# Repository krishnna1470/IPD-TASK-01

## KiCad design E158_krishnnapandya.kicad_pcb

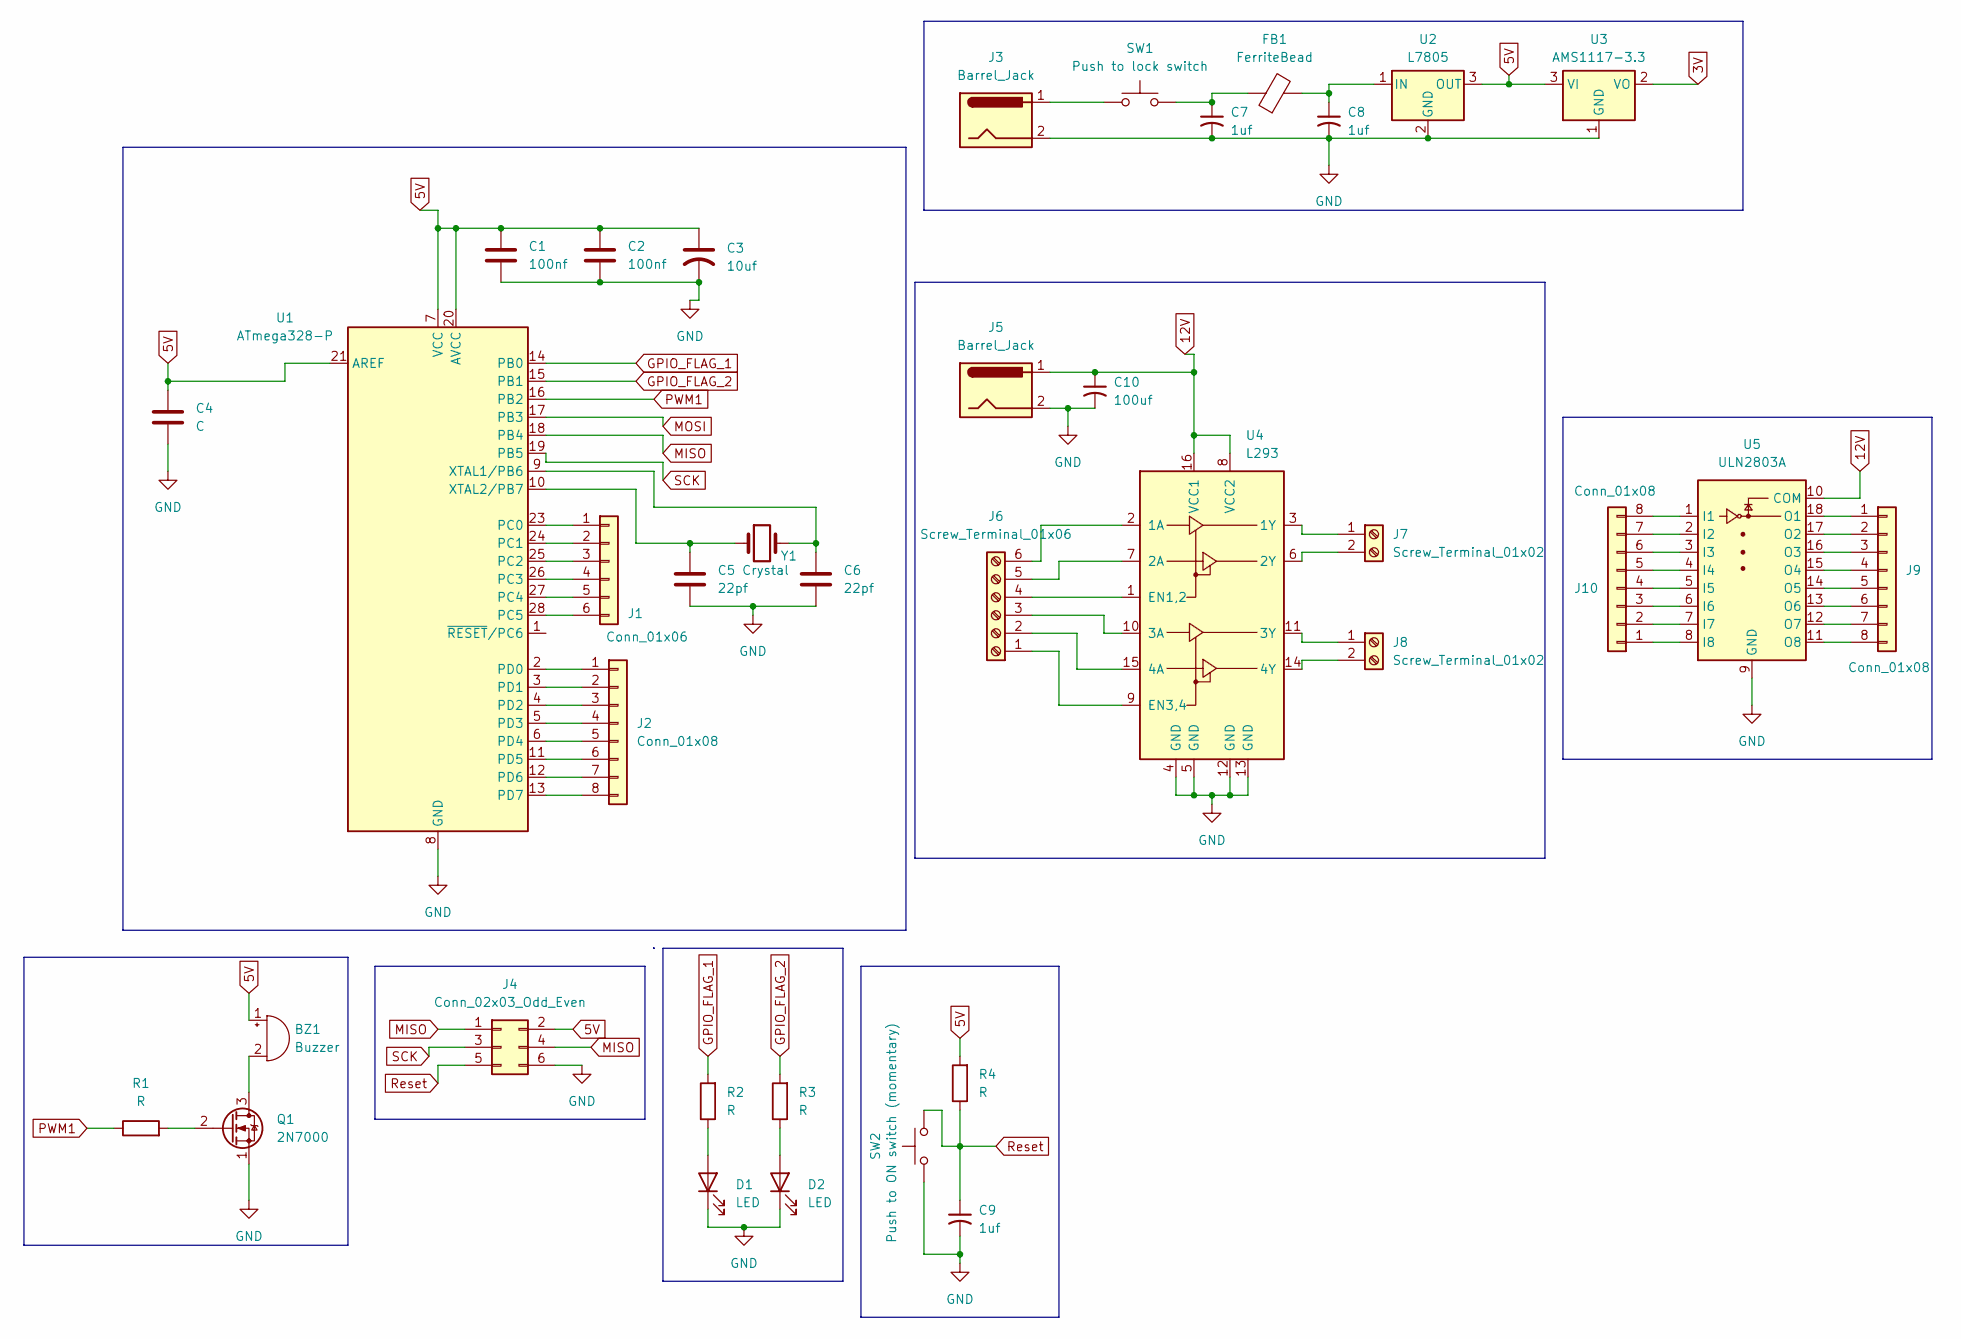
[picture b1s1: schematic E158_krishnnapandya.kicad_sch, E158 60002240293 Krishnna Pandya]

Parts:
BZ1: Buzzer; Buzzer_12x9.5RM7.6
C1, C2: 100nf; C_Disc_D7.0mm_W2.5mm_P5.00mm
C3: 10uf; C_Disc_D7.0mm_W2.5mm_P5.00mm
C4: C; C_Disc_D7.0mm_W2.5mm_P5.00mm
C5, C6: 22pf; C_Disc_D7.0mm_W2.5mm_P5.00mm
C7, C8, C9: 1uf; C_Disc_D7.0mm_W2.5mm_P5.00mm
C10: 100uf; C_Disc_D7.0mm_W2.5mm_P5.00mm
D1, D2: LED; LED_D8.0mm
FB1: FerriteBead; LairdTech_28C0236-0JW-10
J1: Conn_01x06; PinHeader_1x06_P2.54mm_Vertical
J2, J9, J10: Conn_01x08; PinHeader_1x08_P2.54mm_Vertical
J3, J5: Barrel_Jack; BarrelJack_CUI_PJ-063AH_Horizontal
J4: Conn_02x03_Odd_Even; PinHeader_2x03_P2.54mm_Vertical
J6: Screw_Terminal_01x06; TerminalBlock_MaiXu_MX126-5.0-06P_1x06_P5.00mm
J7, J8: Screw_Terminal_01x02; TerminalBlock_MaiXu_MX126-5.0-02P_1x02_P5.00mm
Q1: 2N7000; TO-92_Inline
R1, R2, R3, R4: R; R_Axial_DIN0207_L6.3mm_D2.5mm_P7.62mm_Horizontal
SW1: Push to lock switch; KSA_Tactile_SPST
SW2: Push to ON switch (momentary); KSA_Tactile_SPST
U1: ATmega328-P; DIP-28_W7.62mm
U2: L7805; TO-220-3_Vertical
U3: AMS1117-3.3; SOT-223-3_TabPin2
U4: L293; DIP-16_W7.62mm
U5: ULN2803A; DIP-18_W7.62mm
Y1: Crystal; Crystal_C26-LF_D2.1mm_L6.5mm_Vertical

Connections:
3V: U3.2 (VO)
5V: BZ1.1 (+), C1.1, C2.1, C3.1, C4.1, J4.2, R4.2, U1.7 (VCC), U1.20 (AVCC), U1.21 (AREF), U2.3 (OUT), U3.3 (VI)
12V: C10.1, J5.1, U4.8 (VCC2), U4.16 (VCC1), U5.10 (COM)
GND: C1.2, C2.2, C3.2, C4.2, C5.2, C6.2, C7.2, C8.2, C9.2, C10.2, D1.1 (K), D2.1 (K), J3.2, J4.6, J5.2, Q1.1 (S), SW2.1, U1.8 (GND), U1.22 (GND), U2.2 (GND), U3.1 (GND), U4.4 (GND), U4.5 (GND), U4.12 (GND), U4.13 (GND), U5.9 (GND)
GPIO_FLAG_1: R2.2, U1.14 (PB0)
GPIO_FLAG_2: R3.2, U1.15 (PB1)
MISO: J4.1, J4.4, U1.18 (PB4)
MOSI: U1.17 (PB3)
unnamed: BZ1.2 (-), Q1.3 (D)
unnamed: C7.1, FB1.1, SW1.2
unnamed: D1.2 (A), R2.1
unnamed: D2.2 (A), R3.1
unnamed: J1.1, U1.23 (PC0)
unnamed: J1.2, U1.24 (PC1)
unnamed: J1.3, U1.25 (PC2)
unnamed: J1.4, U1.26 (PC3)
unnamed: J1.5, U1.27 (PC4)
unnamed: J1.6, U1.28 (PC5)
unnamed: J2.1, U1.2 (PD0)
unnamed: J2.2, U1.3 (PD1)
unnamed: J2.3, U1.4 (PD2)
unnamed: J2.4, U1.5 (PD3)
unnamed: J2.5, U1.6 (PD4)
unnamed: J2.6, U1.11 (PD5)
unnamed: J2.7, U1.12 (PD6)
unnamed: J2.8, U1.13 (PD7)
unnamed: J3.1, SW1.1
unnamed: J6.1, U4.9 (EN3,4)
unnamed: J6.2, U4.15 (4A)
unnamed: J6.3, U4.10 (3A)
unnamed: J6.4, U4.1 (EN1,2)
unnamed: J6.5, U4.7 (2A)
unnamed: J6.6, U4.2 (1A)
unnamed: J7.1, U4.3 (1Y)
unnamed: J7.2, U4.6 (2Y)
unnamed: J8.1, U4.11 (3Y)
unnamed: J8.2, U4.14 (4Y)
unnamed: J9.1, U5.18 (O1)
unnamed: J9.2, U5.17 (O2)
unnamed: J9.3, U5.16 (O3)
unnamed: J9.4, U5.15 (O4)
unnamed: J9.5, U5.14 (O5)
unnamed: J9.6, U5.13 (O6)
unnamed: J9.7, U5.12 (O7)
unnamed: J9.8, U5.11 (O8)
unnamed: J10.1, U5.8 (I8)
unnamed: J10.2, U5.7 (I7)
unnamed: J10.3, U5.6 (I6)
unnamed: J10.4, U5.5 (I5)
unnamed: J10.5, U5.4 (I4)
unnamed: J10.6, U5.3 (I3)
unnamed: J10.7, U5.2 (I2)
unnamed: J10.8, U5.1 (I1)
unnamed: Q1.2 (G), R1.2
unnamed: C6.1, U1.9 (XTAL1/PB6), Y1.2
unnamed: C5.1, U1.10 (XTAL2/PB7), Y1.1
unnamed: C8.1, FB1.2, U2.1 (IN)
PWM1: R1.1, U1.16 (PB2)
Reset: C9.1, J4.5, R4.1, SW2.2
SCK: J4.3, U1.19 (PB5)

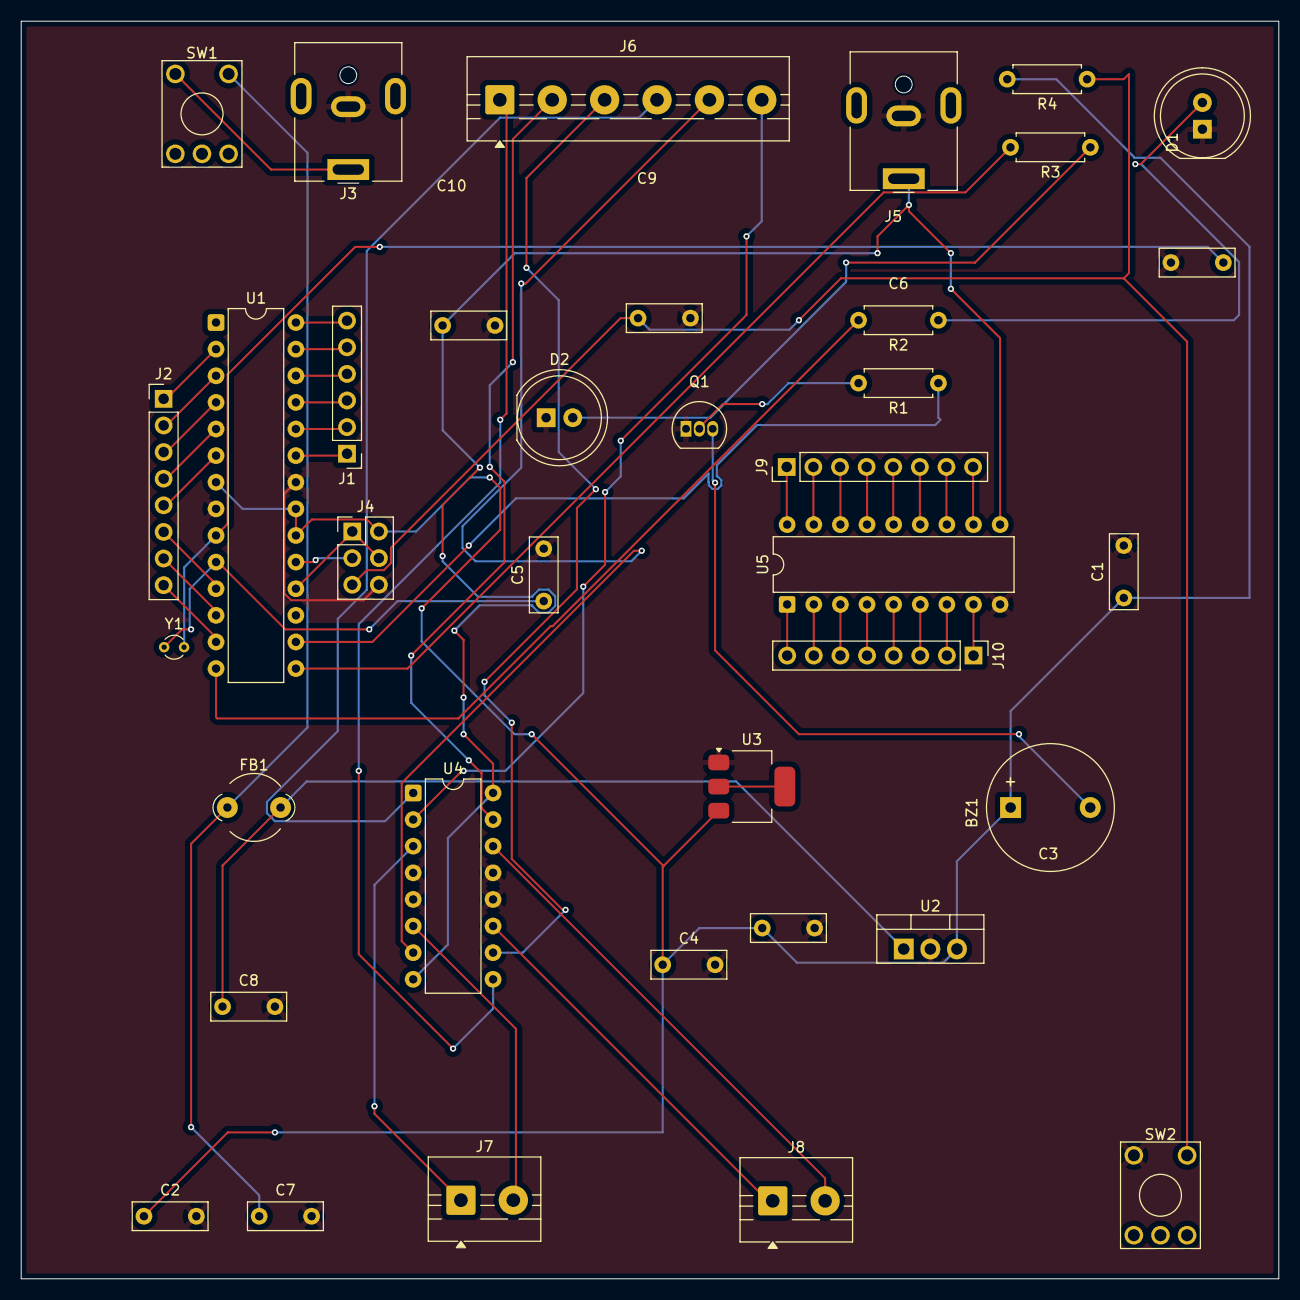
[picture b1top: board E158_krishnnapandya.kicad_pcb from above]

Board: 2 copper layers, 120.0 x 120.0 mm, 37 parts (0 on the bottom side), 58 nets.
